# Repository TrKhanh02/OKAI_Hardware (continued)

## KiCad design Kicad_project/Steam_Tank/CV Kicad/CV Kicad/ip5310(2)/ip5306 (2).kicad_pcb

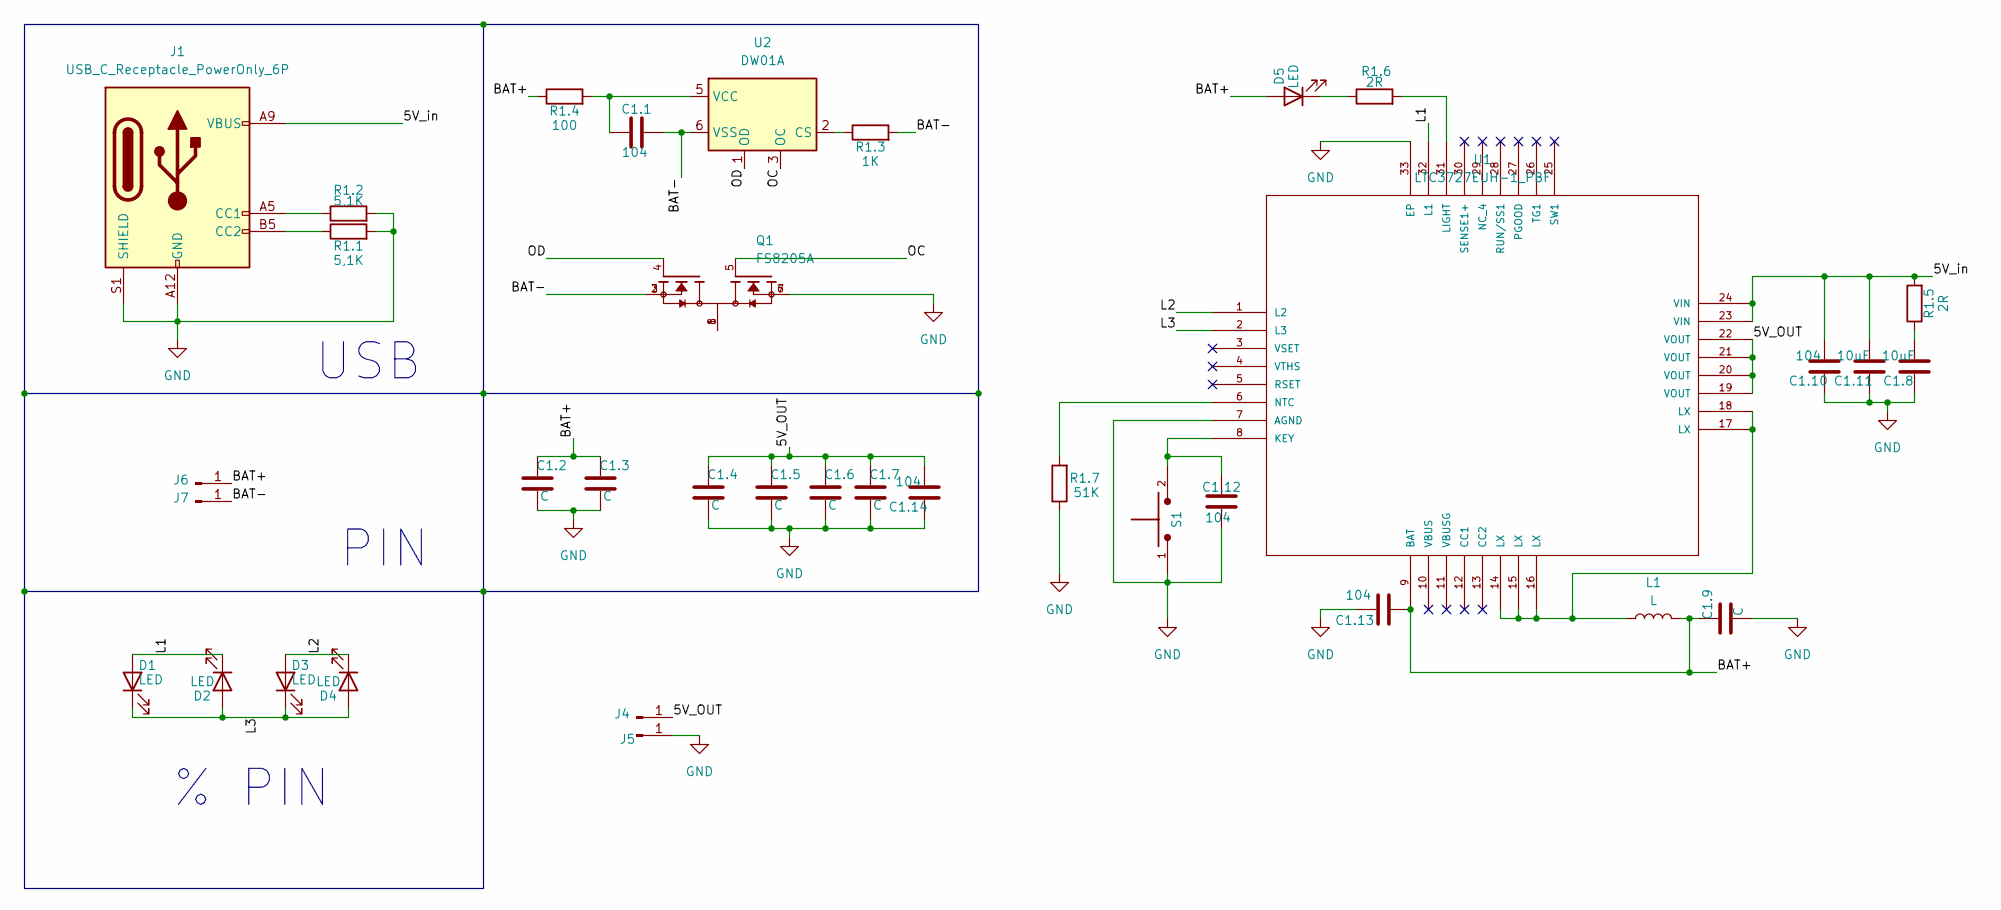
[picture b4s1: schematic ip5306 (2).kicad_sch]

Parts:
C1.1, C1.10, C1.12, C1.13, C1.14: 104; C_0805_2012Metric_Pad1.18x1.45mm_HandSolder
C1.2, C1.3, C1.4, C1.5, C1.6, C1.7, C1.9: C; C_1206_3216Metric_Pad1.33x1.80mm_HandSolder
C1.8, C1.11: 10uF; C_0805_2012Metric_Pad1.18x1.45mm_HandSolder
D1, D2, D3, D4, D5: LED; LED_0805_2012Metric_Pad1.15x1.40mm_HandSolder
J1: USB_C_Receptacle_PowerOnly_6P; USB_C_Receptacle_GCT_USB4125-xx-x_6P_TopMnt_Horizontal
J4, J5, J6, J7: Conn_01x01_Pin; PinSocket_1x01_P2.54mm_Vertical
L1: L; L_7.3x7.3_H4.5
Q1: FS8205A; SOP65P640X120-8N; PARTREV 1.7
R1.1, R1.2: 5,1K; R_0805_2012Metric_Pad1.20x1.40mm_HandSolder
R1.3: 1K; R_0805_2012Metric_Pad1.20x1.40mm_HandSolder
R1.4: 100; R_0805_2012Metric_Pad1.20x1.40mm_HandSolder
R1.5, R1.6: 2R; R_0805_2012Metric_Pad1.20x1.40mm_HandSolder
R1.7: 51K; R_0805_2012Metric_Pad1.20x1.40mm_HandSolder
S1: TS10-63-26-BE-250-SMT-TR; SW_TS10-63-26-BE-250-SMT-TR; PARTREV 1.0
U1: LTC3727EUH-1_PBF; QFN-32_UH; MANUFACTURER_PART_NUMBER ltc3727euh1
U2: DW01A; SOT-23-6

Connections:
/5V_OUT: C1.4.1, C1.5.1, C1.6.1, C1.7.1, C1.14.2, J4.1, U1.19 (VOUT), U1.20 (VOUT), U1.21 (VOUT), U1.22 (VOUT)
/5V_in: C1.10.2, C1.11.2, J1.A9 (VBUS), J1.B9 (VBUS), R1.5.2, U1.23 (VIN), U1.24 (VIN)
/BAT+: C1.2.1, C1.3.1, C1.9.1, C1.13.1, D5.2 (A), J6.1, L1.2, R1.4.1, U1.9 (BAT)
/BAT-: C1.1.2, J7.1, Q1.2, Q1.3, R1.3.2, U2.6 (VSS)
/L1: D1.2 (A), D2.1 (K), U1.32 (L1)
/L2: D3.2 (A), D4.1 (K), U1.1 (L2)
/L3: D1.1 (K), D2.2 (A), D3.1 (K), D4.2 (A), U1.2 (L3)
/OC: Q1.5, U2.3 (OC)
/OD: Q1.4, U2.1 (OD)
GND: C1.2.2, C1.3.2, C1.4.2, C1.5.2, C1.6.2, C1.7.2, C1.8.1, C1.9.2, C1.10.1, C1.11.1, C1.12.1, C1.13.2, C1.14.1, J1.A12 (GND), J1.B12 (GND), J1.S1 (SHIELD), J5.1, Q1.6, Q1.7, R1.1.2, R1.2.2, R1.7.1, S1.1, U1.7 (AGND), U1.33 (EP)
unnamed: C1.8.2, R1.5.1
unnamed: D5.1 (K), R1.6.1
unnamed: J1.A5 (CC1), R1.2.1
unnamed: J1.B5 (CC2), R1.1.1
unnamed: L1.1, U1.14 (LX), U1.15 (LX), U1.16 (LX), U1.17 (LX), U1.18 (LX)
unnamed: Q1.1, Q1.8
unnamed: C1.12.2, S1.2, U1.8 (KEY)
unnamed: R1.6.2, U1.31 (LIGHT)
unnamed: R1.7.2, U1.6 (NTC)
unnamed: R1.3.1, U2.2 (CS)
unnamed: C1.1.1, R1.4.2, U2.5 (VCC)

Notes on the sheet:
PIN
% PIN
USB

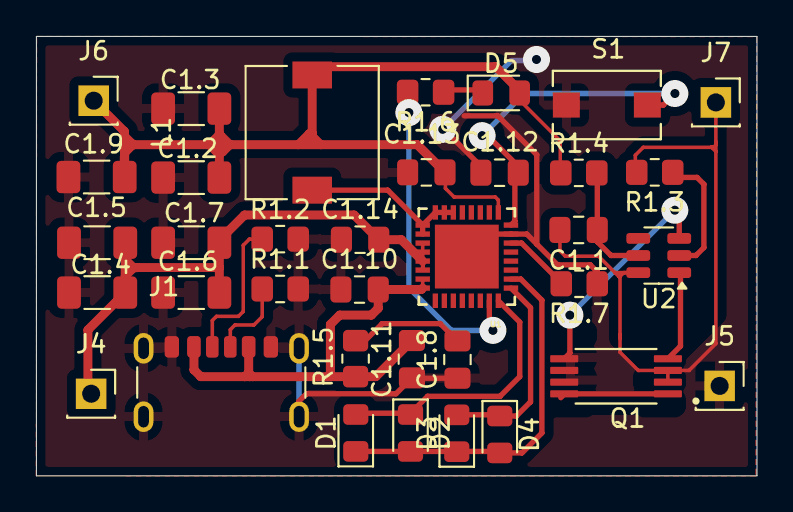
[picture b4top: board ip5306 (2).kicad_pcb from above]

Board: 2 copper layers, 40.0 x 24.4 mm, 36 parts (0 on the bottom side), 21 nets.

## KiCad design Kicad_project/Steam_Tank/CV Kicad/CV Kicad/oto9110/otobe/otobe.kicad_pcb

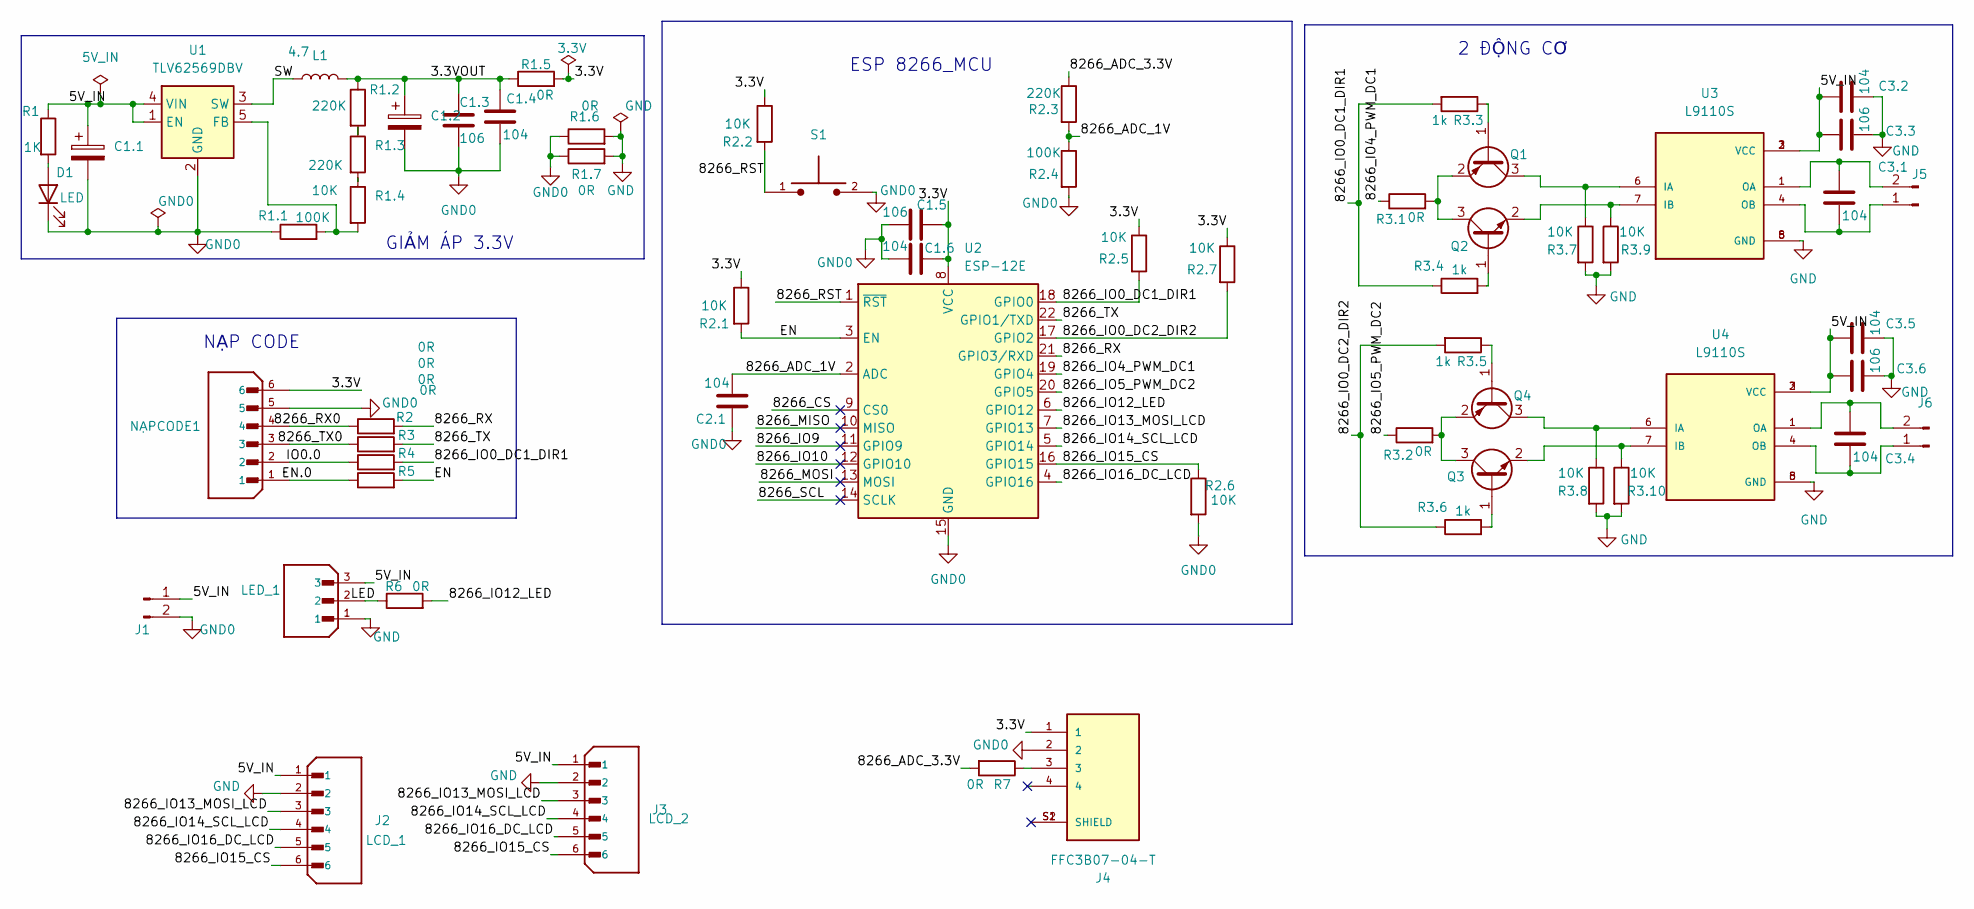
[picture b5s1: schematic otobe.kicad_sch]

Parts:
C1.1, C1.2: C_Polarized; CP_Elec_6.3x5.3
C1.3, C1.5, C3.3, C3.6: 106; C_0805_2012Metric
C1.4, C1.6, C2.1, C3.1, C3.2, C3.4, C3.5: 104; C_0805_2012Metric
D1: LED; LED_0805_2012Metric
J1, J5, J6: Conn_01x02_Pin; PinHeader_1x02_P2.54mm_Vertical
J2: LCD_1; JST_B6B-XH-A_LF__SN_; PARTREV 7/4/21
J3: LCD_2; JST_B6B-XH-A_LF__SN_; PARTREV 7/4/21
J4: FFC3B07-04-T; GCT_FFC3B07-04-T; PARTREV A
L1: 4.7; L_6.3x6.3_H3
LED_1: B3B-XH-A; JST_B3B-XH-A; PARTREV 7/4/21
NẠPCODE1: B6B-XH-A_LF__SN_; PinHeader_1x06_P2.54mm_Vertical; PARTREV 7/4/21
Q1, Q4: SS8550; SOT-23
Q2, Q3: SS8050; SOT-23
R1: 1K; R_0805_2012Metric_Pad1.20x1.40mm_HandSolder
R1.1, R2.4: 100K; R_0805_2012Metric_Pad1.20x1.40mm_HandSolder
R1.2, R1.3, R2.3: 220K; R_0805_2012Metric_Pad1.20x1.40mm_HandSolder
R1.4, R2.1, R2.2, R2.5, R2.6, R2.7, R3.7, R3.8, R3.9, R3.10: 10K; R_0805_2012Metric_Pad1.20x1.40mm_HandSolder
R1.5, R1.6, R1.7, R2, R3, R3.1, R3.2, R4, R5, R6, R7: 0R; R_0805_2012Metric_Pad1.20x1.40mm_HandSolder
R3.3, R3.4, R3.5, R3.6: 1k; R_0805_2012Metric_Pad1.20x1.40mm_HandSolder
S1: TS10-63-26-BE-250-SMT-TR; SW_TS10-63-26-BE-250-SMT-TR; PARTREV 1.0
U1: TLV62569DBV; SOT-23-5
U2: ESP-12E
U3, U4: L9110S; SOIC127P599X172-8N; PARTREV NA

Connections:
/3.3V: C1.5.1, C1.6.2, J4.1, NẠPCODE1.6, R1.5.2, R2.1.1, R2.2.1, R2.5.1, R2.7.1, U2.8 (VCC)
/3.3VOUT: C1.2.1, C1.3.1, C1.4.1, L1.2, R1.2.1, R1.5.1
/5V_IN: C1.1.1, C3.2.1, C3.3.1, C3.5.1, C3.6.1, J1.1, J2.1, J3.1, LED_1.3, R1.1, U1.1 (EN), U1.4 (VIN), U3.2 (VCC), U3.3 (VCC), U4.2 (VCC), U4.3 (VCC)
/8266_ADC_1V: C2.1.2, R2.3.2, R2.4.1, U2.2 (ADC)
/8266_ADC_3.3V: R2.3.1, R7.2
/8266_CS: U2.9 (CS0)
/8266_IO0_DC1_DIR1: R2.5.2, R3.3.2, R3.4.1, R4.2, U2.18 (GPIO0)
/8266_IO0_DC2_DIR2: R2.7.2, R3.5.2, R3.6.1, U2.17 (GPIO2)
/8266_IO4_PWM_DC1: R3.1.1, U2.19 (GPIO4)
/8266_IO5_PWM_DC2: R3.2.1, U2.20 (GPIO5)
/8266_IO9: U2.11 (GPIO9)
/8266_IO10: U2.12 (GPIO10)
/8266_IO12_LED: R6.2, U2.6 (GPIO12)
/8266_IO13_MOSI_LCD: J2.3, J3.3, U2.7 (GPIO13)
/8266_IO14_SCL_LCD: J2.4, J3.4, U2.5 (GPIO14)
/8266_IO15_CS: J2.6, J3.6, R2.6.1, U2.16 (GPIO15)
/8266_IO16_DC_LCD: J2.5, J3.5, U2.4 (GPIO16)
/8266_MISO: U2.10 (MISO)
/8266_MOSI: U2.13 (MOSI)
/8266_RST: R2.2.2, S1.1, U2.1 (~RST)
/8266_RX: R2.2, U2.21 (GPIO3/RXD)
/8266_RX0: NẠPCODE1.4, R2.1
/8266_SCL: U2.14 (SCLK)
/8266_TX: R3.2, U2.22 (GPIO1/TXD)
/8266_TX0: NẠPCODE1.3, R3.1
/EN: R2.1.2, R5.2, U2.3 (EN)
/EN.0: NẠPCODE1.1, R5.1
/IO0.0: NẠPCODE1.2, R4.1
/LED: LED_1.2, R6.1
/SW: L1.1, U1.3 (SW)
GND: C3.2.2, C3.3.2, C3.5.2, C3.6.2, J2.2, J3.2, LED_1.1, R1.6.2, R1.7.2, R3.7.2, R3.8.2, R3.9.2, R3.10.2, U3.5 (GND), U3.8 (GND), U4.5 (GND), U4.8 (GND)
GND0: C1.1.2, C1.2.2, C1.3.2, C1.4.2, C1.5.2, C1.6.1, C2.1.1, D1.1 (K), J1.2, J4.2, NẠPCODE1.5, R1.1.1, R1.6.1, R1.7.1, R2.4.2, R2.6.2, S1.2, U1.2 (GND), U2.15 (GND)
unnamed: D1.2 (A), R1.2
unnamed: J4.3, R7.1
unnamed: C3.1.2, J5.1, U3.4 (OB)
unnamed: C3.1.1, J5.2, U3.1 (OA)
unnamed: C3.4.2, J6.1, U4.4 (OB)
unnamed: C3.4.1, J6.2, U4.1 (OA)
unnamed: Q1.1 (B), R3.3.1
unnamed: Q1.3 (C), R3.7.1, U3.6 (IA)
unnamed: Q1.2 (E), Q2.3 (C), R3.1.2
unnamed: Q2.1 (B), R3.4.2
unnamed: Q2.2 (E), R3.9.1, U3.7 (IB)
unnamed: Q3.1 (B), R3.6.2
unnamed: Q3.3 (C), Q4.2 (E), R3.2.2
unnamed: Q3.2 (E), R3.10.1, U4.7 (IB)
unnamed: Q4.1 (B), R3.5.1
unnamed: Q4.3 (C), R3.8.1, U4.6 (IA)
unnamed: R1.2.2, R1.3.1
unnamed: R1.3.2, R1.4.1
unnamed: R1.1.2, R1.4.2, U1.5 (FB)

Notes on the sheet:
NẠP CODE
ESP 8266_MCU
GIẢM ÁP 3.3V
2 ĐỘNG CƠ

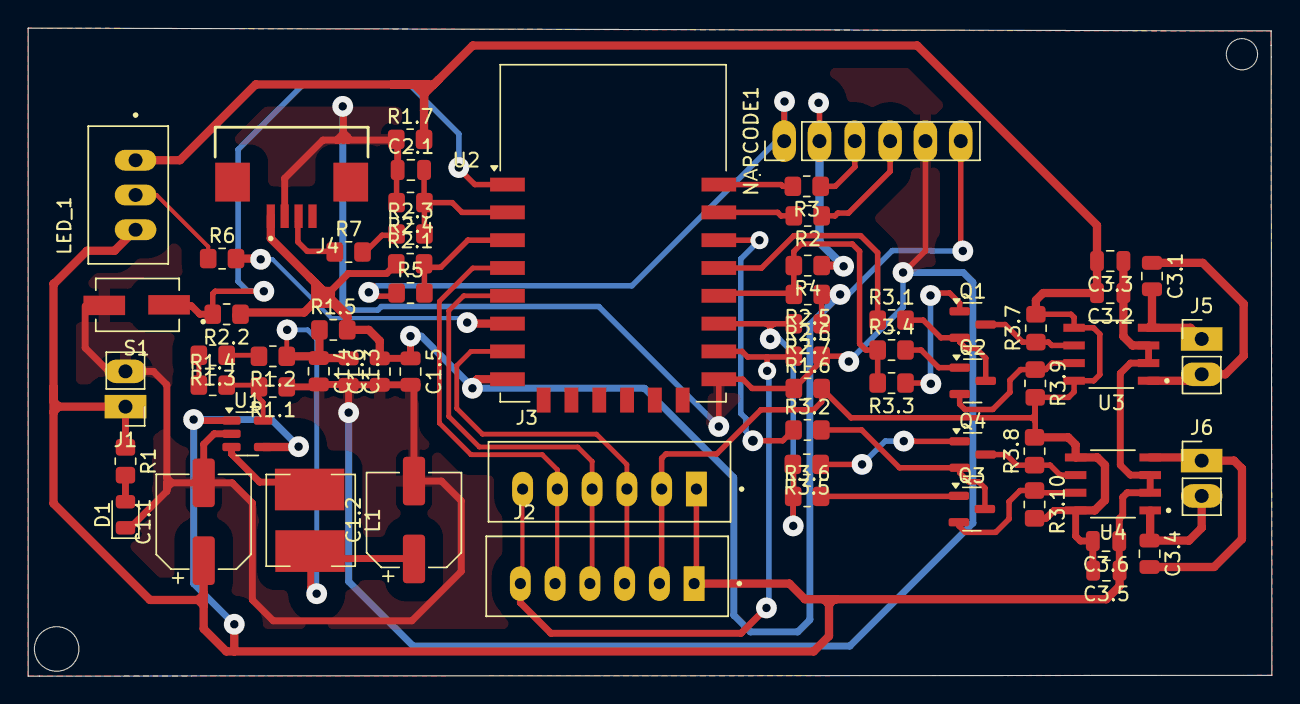
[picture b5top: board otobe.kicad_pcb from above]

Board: 2 copper layers, 89.4 x 46.6 mm, 63 parts (0 on the bottom side), 45 nets.
